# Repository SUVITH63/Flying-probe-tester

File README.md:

# FPTester

> **Automated Flying Probe PCB Evaluation & Kinematics Engine**

**FPTester** is an automated dual-arm flying probe PCB evaluation application. It parses KiCad (`.kicad_pcb`) and Gerber (`.gbr`) design files, generates hardware-ready test plan sequences, and provides a 2D dual 5-bar linkage kinematics visualizer with interactive flex handles.

---

## 💾 Direct 1-Click Downloads & Releases

Click below to download the application for your operating system:

| Operating System | Direct Download Link | Format | Launch Instructions |
| :--- | :--- | :--- | :--- |
| 🪟 **Windows** | [**Download FPTester for Windows (.zip)**](https://github.com/SUVITH63/Flying-probe-tester/releases/download/v1.1.0/FPTester-Windows-x64.zip) | 1-Click Portable `.zip` | Extract zip and double-click `start_windows.bat` or `FPTester-Launcher.bat` |
| 🪟 **Windows** | [**Download Standalone FPTester.exe**](https://github.com/SUVITH63/Flying-probe-tester/releases/download/v1.1.0/FPTester-Windows.exe) | Single Executable `.exe` | Double-click `FPTester-Windows.exe` |
| 🍎 **macOS** | [**Download FPTester for macOS (.zip)**](https://github.com/SUVITH63/Flying-probe-tester/releases/download/v1.1.0/FPTester-macOS-1Click.zip) | Standalone `.zip` | Extract zip and double-click `start_mac.command` |

> 🍎 **Mac Gatekeeper Tip**: If macOS displays *"Apple could not verify FPTester-App"*, double-click **`start_mac.command`** (which automatically unlocks it) OR right-click `FPTester-App` -> select **Open** -> click **Open Anyway**.

---

## ✨ Key Features

- **Embedded Local LLM Engine (`llm/local_llm.py`)**: Zero-dependency offline AI inference for power rails, GND, I2C pull-ups, and signal traces out of the box without requiring API keys or external Ollama setup.
- **Built-in Zero-Dependency Web Engine**: Native HTTP server running out-of-the-box on port 8000.
- **Dual 5-Bar Kinematics Visualizer**: Interactive canvas with real-time inverse kinematics, articulated elbow joints, and drag-and-drop flex handles.
- **Hardware & Simulation Support**: Interactive probe execution and ESP32 USB hardware dispatch protocol.

---

## 🚀 Running from Source

```bash
git clone https://github.com/SUVITH63/Flying-probe-tester.git
cd Flying-probe-tester

# Launch cross-platform application
python3 run_app.py
```

### OS Specific Launchers
- **Windows**: Double-click `start_windows.bat` or `FPTester-Launcher.bat`
- **macOS / Linux**: Double-click `start_mac.command` or `./start_mac_linux.sh`

Application will open automatically in your web browser at **http://localhost:8000**.

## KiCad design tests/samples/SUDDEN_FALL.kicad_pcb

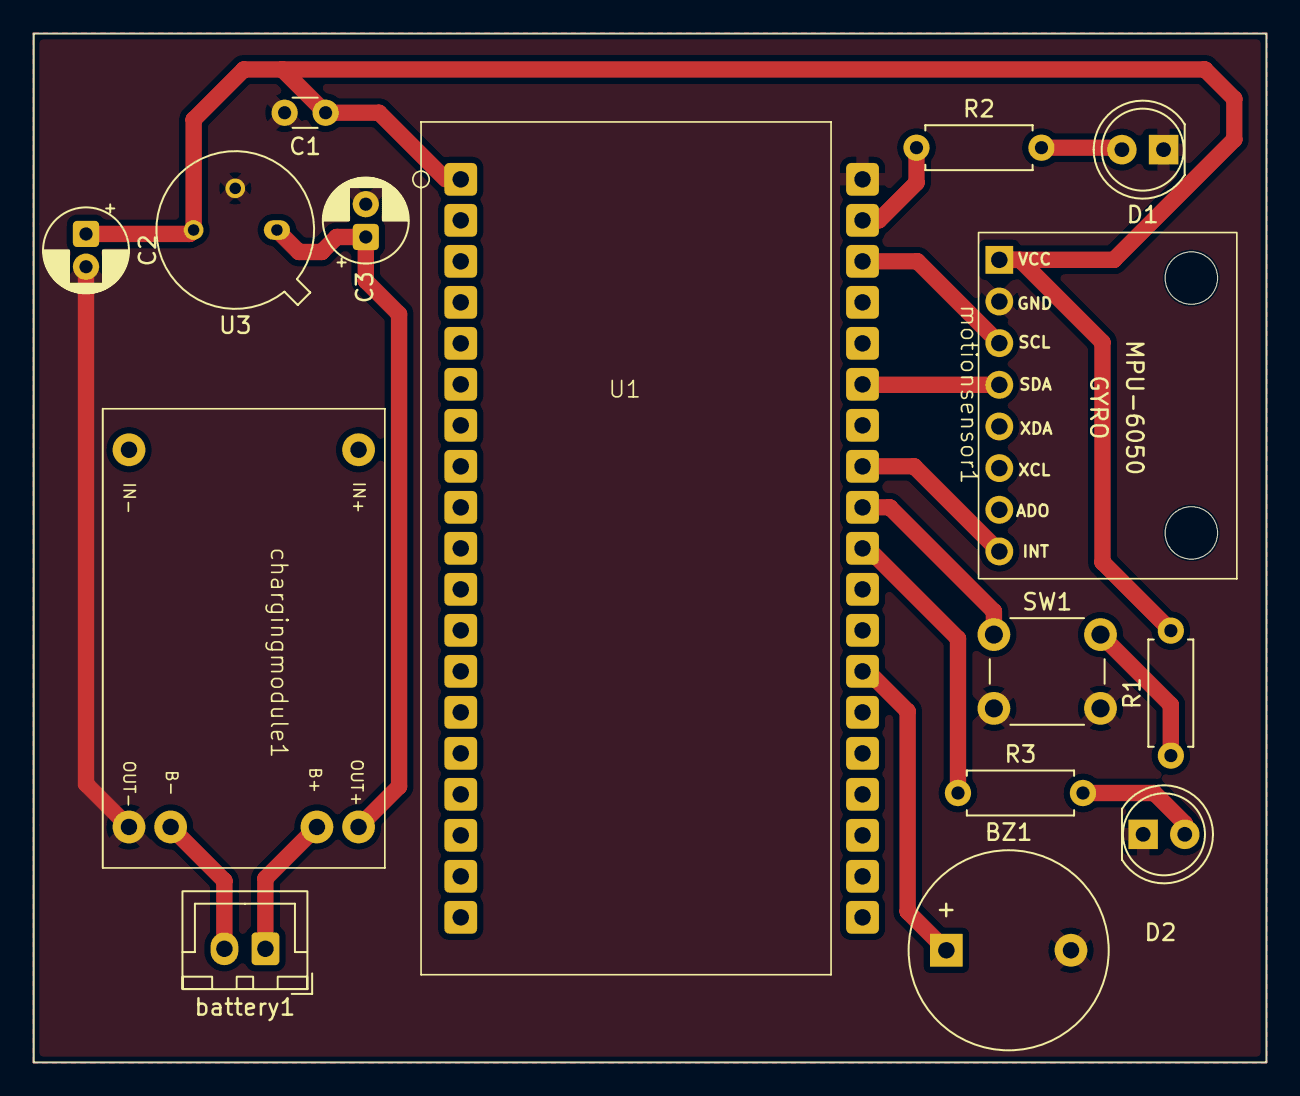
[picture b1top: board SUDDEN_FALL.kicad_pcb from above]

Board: 2 copper layers, 75.2 x 62.8 mm, 15 parts (0 on the bottom side), 15 nets.

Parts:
BZ1: Buzzer; Buzzer_12x9.5RM7.6
C1: 0.1uF; C_Disc_D3.0mm_W1.6mm_P2.50mm
C2, C3: 10uF; CP_Radial_D5.0mm_P2.00mm
D1: red LED; LED_D5.0mm
D2: green LED; LED_D5.0mm
R1: 10K; R_Axial_DIN0207_L6.3mm_D2.5mm_P7.62mm_Horizontal
R2, R3: 2.2K; R_Axial_DIN0207_L6.3mm_D2.5mm_P7.62mm_Horizontal
SW1: SW_Push_Dual; SW_PUSH_6mm
U1: ESP32 CP2102; NEW ESP 38PIN
U3: LM117_TO39; TO-39-3
battery1: Conn_01x02; JST_XH_B2B-XH-A_1x02_P2.50mm_Vertical
chargingmodule1: Conn_01x06; TP-4056
motionsensor1: Conn_01x08; GYRO MIRRORED NEW

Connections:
GND: BZ1.2 (-), C1.2, C2.2, C3.2, D1.1 (K), D2.1 (K), SW1.3, SW1.4, U1.38 (GND), U3.2 (GND), chargingmodule1.4 (OUT-), motionsensor1.2 (GND)
unnamed: BZ1.1 (+), U1.26 (GPIO4)
unnamed: D1.2 (A), R2.2
unnamed: D2.2 (A), R3.2
unnamed: R1.1, SW1.2
unnamed: C1.1, C2.1, R1.2, U1.1 (3V3), U3.3 (VO), motionsensor1.1 (VCC)
unnamed: R3.1, U1.29 (GPIO5)
unnamed: SW1.1, U1.30 (GPIO18)
unnamed: U1.31 (GPIO19), motionsensor1.8 (INT)
unnamed: U1.33 (GPIO21), motionsensor1.4 (SDA)
unnamed: U1.36 (GPIO22), motionsensor1.3 (SCL)
unnamed: R2.1, U1.37 (GPIO23)
unnamed: C3.1, U3.1 (VI), chargingmodule1.3 (OUT+)
unnamed: battery1.1 (B+), chargingmodule1.5 (B+)
unnamed: battery1.2 (B-), chargingmodule1.6 (B-)

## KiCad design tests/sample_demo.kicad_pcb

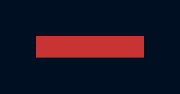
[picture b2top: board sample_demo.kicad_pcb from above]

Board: 0 copper layers, 3 parts (0 on the bottom side), 2 nets, no tracks yet.

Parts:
C1: 100nF; C_0805_2012Metric
R1, R2: 10k; R_0805_2012Metric

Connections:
+3V3: C1.2, R1.2, R2.2
SDA: R1.1, R2.1

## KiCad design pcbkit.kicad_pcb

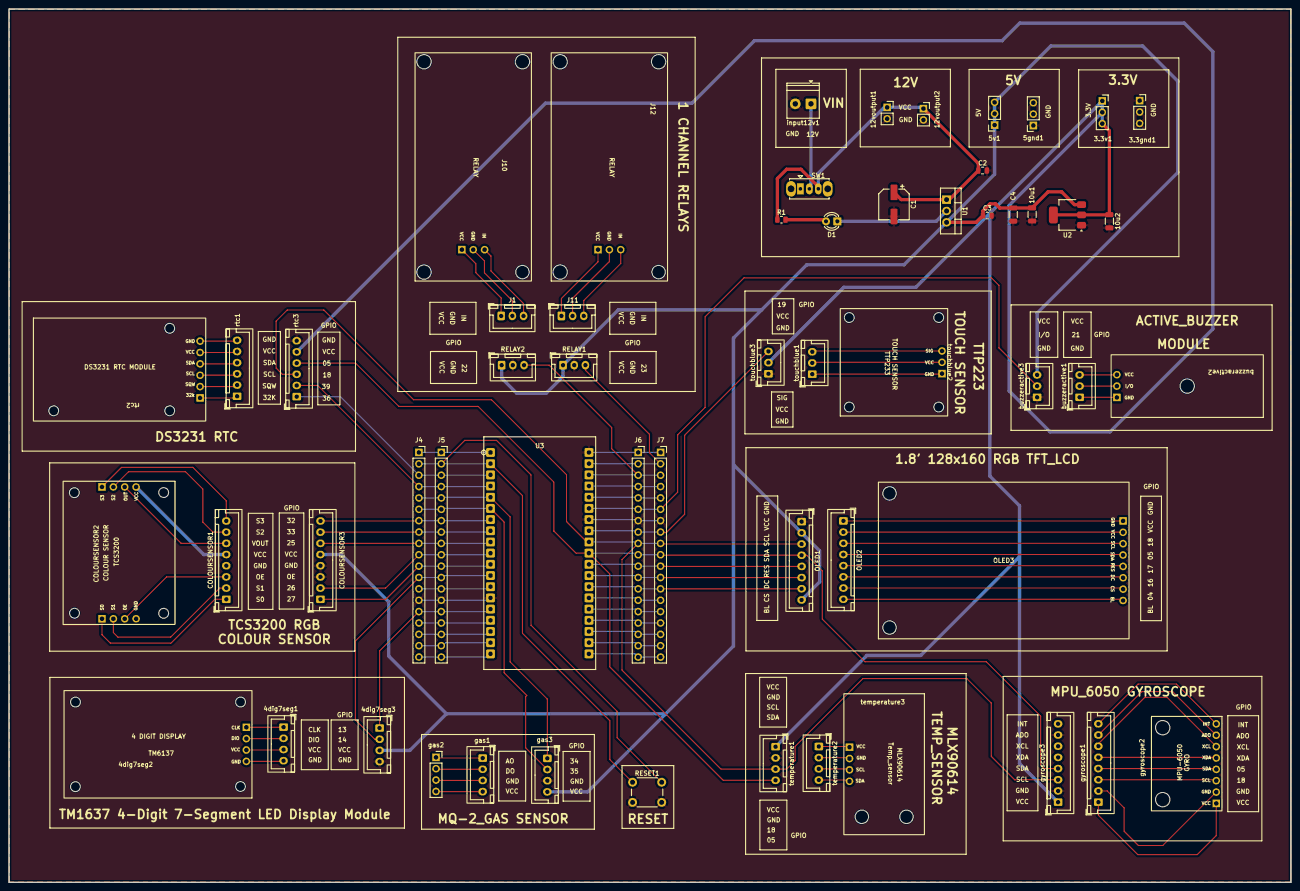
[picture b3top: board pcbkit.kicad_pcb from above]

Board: 2 copper layers, 286.4 x 195.1 mm, 57 parts (0 on the bottom side), 95 nets.

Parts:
3.3gnd1, 3.3v1, 5gnd1, 5v1: Conn_01x03; PinSocket_1x03_P2.54mm_Vertical
4dig7seg1, 4dig7seg3: Conn_01x04; JST_XH_B4B-XH-A_1x04_P2.50mm_Vertical
4dig7seg2: Conn_01x04; 4digit display
10u1, 10u2: C_Small_US; C_1206_3216Metric
12voutput1, 12voutput2: Conn_01x02; PinSocket_1x02_P2.54mm_Vertical
C1: 220u; CP_Elec_6.3x7.7
C2: 0.33uF; C_0805_2012Metric
C3: 0.1uF; C_0805_2012Metric
C4: 10uF; C_1206_3216Metric
COLOURSENSOR1, COLOURSENSOR3: Conn_02x04_Counter_Clockwise; JST_XH_B8B-XH-A_1x08_P2.50mm_Vertical
COLOURSENSOR2: Conn_02x04_Counter_Clockwise; coloursensor final
D1: LED; LED_D3.0mm
J1, J11: Conn_01x03; JST_XH_B3B-XH-A_1x03_P2.50mm_Vertical
J4, J5, J6, J7: Conn_01x19; PinSocket_1x19_P2.54mm_Vertical
J10, J12: Conn_01x03; relay1
OLED1, OLED2: Conn_01x08; JST_XH_B8B-XH-A_1x08_P2.50mm_Vertical
OLED3: Conn_01x08; OLED128x160 1.8inch tft module
R1: 560; R_0805_2012Metric
RELAY1, RELAY2: Conn_01x03; JST_XH_B3B-XH-A_1x03_P2.50mm_Vertical
RESET1: SW_Push_Dual; SW_PUSH_6mm
SW1: SW_SPDT; SW_Slide_SPDT_Straight_CK_OS102011MS2Q
U1: LM7805_TO220; TO-220-3_Vertical
U2: LM1117S-3.3; SOT-223-3_TabPin2
U3: ESP32 CP2102; ESP32_38Pin
buzzeractive1, buzzeractive3: Conn_01x03; JST_XH_B3B-XH-A_1x03_P2.50mm_Vertical
buzzeractive2: Conn_01x03; buzzer_finalmodule
gas1, gas3: Conn_01x04; JST_XH_B4B-XH-A_1x04_P2.50mm_Vertical
gas2: Conn_01x04; PinSocket_1x04_P2.54mm_Vertical
gyroscope1, gyroscope3: Conn_01x08; JST_XH_B8B-XH-A_1x08_P2.50mm_Vertical
gyroscope2: Conn_01x08; GYROSCOPE_MODULE
input12v1: Conn_01x02; TerminalBlock_Phoenix_PT-1,5-2-3.5-H_1x02_P3.50mm_Horizontal
rtc1, rtc3: Conn_01x06; JST_XH_B6B-XH-A_1x06_P2.50mm_Vertical
rtc2: Conn_01x06; RTC
temperature1, temperature2: Conn_01x04; JST_XH_B4B-XH-A_1x04_P2.50mm_Vertical
temperature3: Conn_01x04; MLX90614
touchblue1, touchblue3: Conn_01x03; JST_XH_B3B-XH-A_1x03_P2.50mm_Vertical
touchblue2: Conn_01x03; TPP233

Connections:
GND: 3.3gnd1.1 (GND), 3.3gnd1.2 (GND), 3.3gnd1.3 (GND), 4dig7seg3.4 (GND), 5gnd1.1 (GND), 5gnd1.2 (GND), 5gnd1.3 (GND), 10u1.2, 10u2.2, 12voutput1.2 (GND), 12voutput2.2 (GND), C1.2, C2.2, C3.2, C4.2, COLOURSENSOR3.3 (OE), COLOURSENSOR3.4 (GND), D1.1 (K), J4.14, J5.14, J6.1, J6.7, J7.1, J7.7 (87Pin_7), OLED1.1 (GND), RELAY1.2 (GND), RELAY2.2 (GND), RESET1.2 (GND), U1.2 (GND), U2.1 (GND), U3.14 (GND), U3.32 (GND), U3.38 (GND), buzzeractive3.1 (GND), gas3.3 (GND), gyroscope3.2 (GND), gyroscope3.7 (ADD), input12v1.2 (GND), rtc3.6 (GND), temperature1.2 (GND), touchblue3.1 (GND)
unnamed: 4dig7seg1.1 (CLK), 4dig7seg2.1 (CLK)
unnamed: 4dig7seg1.2 (DIO), 4dig7seg2.2 (DIO)
unnamed: 4dig7seg1.4 (GND), 4dig7seg2.4 (GND)
unnamed: 4dig7seg1.3 (VCC), 4dig7seg2.3 (VCC)
unnamed: 4dig7seg3.1 (CLK), J4.15, J5.15, U3.15 (GPIO13)
unnamed: 4dig7seg3.2 (DIO), J4.12, J5.12, U3.12 (GPIO14)
unnamed: 4dig7seg3.3 (VCC), 5v1.1 (5V), 5v1.2 (5V), 5v1.3 (5V), 10u1.1, C3.1, C4.1, COLOURSENSOR3.5 (VCC), OLED1.2 (VCC), OLED1.8 (BL), RELAY1.1 (VCC), RELAY2.1 (VCC), U1.3 (VO), U2.3 (VI), buzzeractive3.3 (VCC), gas3.4 (VCC)
unnamed: 12voutput1.1 (12V_OUT), 12voutput2.1 (12V_OUT), C1.1, C2.1, R1.1, SW1.3 (C), U1.1 (VI)
unnamed: COLOURSENSOR1.4 (GND), COLOURSENSOR2.4 (GND)
unnamed: COLOURSENSOR1.3 (OE), COLOURSENSOR2.3 (OE)
unnamed: COLOURSENSOR1.2 (S1), COLOURSENSOR2.2 (S1)
unnamed: COLOURSENSOR1.7 (S2), COLOURSENSOR2.7 (S2)
unnamed: COLOURSENSOR1.8 (S3), COLOURSENSOR2.8 (S3)
unnamed: COLOURSENSOR1.1 (SO), COLOURSENSOR2.1 (SO)
unnamed: COLOURSENSOR1.5 (VCC), COLOURSENSOR2.5 (VCC)
unnamed: COLOURSENSOR1.6 (VOUT), COLOURSENSOR2.6 (VOUT)
unnamed: COLOURSENSOR3.2 (S1), J4.10, J5.10, U3.10 (GPIO26)
unnamed: COLOURSENSOR3.7 (S2), J4.8, J5.8, U3.8 (GPIO33)
unnamed: COLOURSENSOR3.8 (S3), J4.7, J5.7, U3.7 (GPIO32)
unnamed: COLOURSENSOR3.1 (SO), J4.11, J5.11, U3.11 (GPIO27)
unnamed: COLOURSENSOR3.6 (VOUT), J4.9, J5.9, U3.9 (GPIO25)
unnamed: D1.2 (A), R1.2
unnamed: J1.2 (GND), J10.2 (GND)
unnamed: J1.3 (IN), J10.3 (IN)
unnamed: J1.1 (VCC), J10.1 (VCC)
unnamed: J4.1, J5.1, U3.1 (3V3)
unnamed: J4.2, J5.2, RESET1.1 (EN), U3.2 (EN)
unnamed: J4.3, J5.3, U3.3 (GPIO36), rtc3.1 (32K)
unnamed: J4.4, J5.4, U3.4 (GPIO39), rtc3.2 (SQW)
unnamed: J4.5, J5.5, U3.5 (GPIO34), gas3.1 (A0)
unnamed: J4.6, J5.6, U3.6 (GPIO35), gas3.2 (DO)
unnamed: J4.13, J5.13, U3.13 (GPIO12)
unnamed: J4.16, J5.16, U3.16 (GPIO9_/_SO2)
unnamed: J4.17, J5.17, U3.17 (GPIO10__/_S03)
unnamed: J4.18, J5.18, U3.18 (GPIO11_/_CMD)
unnamed: J4.19, J5.19, U3.19 (V5)
unnamed: J6.19 (1Pin_19), J7.19, U3.20 (GPIO6_/_CLK)
unnamed: J6.2 (2Pin_2), J7.2, RELAY1.3 (IN), U3.37 (GPIO23)
unnamed: J6.3, J7.3, RELAY2.3 (IN), U3.36 (GPIO22)
unnamed: J6.4, J7.4, U3.35 (GPIO1_/_TXD)
unnamed: J6.5, J7.5, U3.34 (GPIO3_/_RXD)
unnamed: J6.6, J7.6, U3.33 (GPIO21), buzzeractive3.2 (I/O)
unnamed: J6.8, J7.8, U3.31 (GPIO19), touchblue3.3 (SIG)
unnamed: J6.9, J7.9, OLED1.3 (CLK/SCL), U3.30 (GPIO18), gyroscope3.3 (SCL), rtc3.3 (SCL), temperature1.3 (SCL)
unnamed: J6.10, J7.10 (1Pin_10), OLED1.4 (SDA/MOSI/DIN), U3.29 (GPIO5), gyroscope3.4 (SDA), rtc3.4 (SDA), temperature1.4 (SDA)
unnamed: J6.11, J7.11, OLED1.5 (RES), U3.28 (GPIO17)
unnamed: J6.12, J7.12, OLED1.6 (DC), U3.27 (GPIO16)
unnamed: J6.13, J7.13, OLED1.7 (CS), U3.26 (GPIO4)
unnamed: J6.15, J7.15, U3.24 (GPIO2)
unnamed: J6.16, J7.16, U3.23 (GPIO15)
unnamed: J6.17, J7.17, U3.22 (GPIO8__/_SD1)
unnamed: J6.18, J7.18, U3.21 (GPIO7__/_SD0)
unnamed: J6.14, J7.14, U3.25 (GPIO0)
unnamed: J11.2 (GND), J12.2 (GND)
unnamed: J11.3 (IN), J12.3 (IN)
unnamed: J11.1 (VCC), J12.1 (VCC)
unnamed: OLED2.8 (BL), OLED3.8 (BL)
unnamed: OLED2.3 (CLK/SCL), OLED3.3 (CLK/SCL)
unnamed: OLED2.7 (CS), OLED3.7 (CS)
unnamed: OLED2.6 (DC), OLED3.6 (DC)
unnamed: OLED2.1 (GND), OLED3.1 (GND)
unnamed: OLED2.5 (RES), OLED3.5 (RES)
unnamed: OLED2.4 (SDA/MOSI/DIN), OLED3.4 (SDA/MOSI/DIN)
unnamed: OLED2.2 (VCC), OLED3.2 (VCC)
unnamed: SW1.2 (B), input12v1.1 (12V_IN)
unnamed: 3.3v1.1 (3.3V), 3.3v1.2 (3.3V), 3.3v1.3 (3.3V), 10u2.1, U2.2 (VO), gyroscope3.1 (VCC), rtc3.5 (VCC), temperature1.1 (VCC), touchblue3.2 (VCC)
unnamed: buzzeractive1.1 (GND), buzzeractive2.1 (GND)
unnamed: buzzeractive1.2 (I/O), buzzeractive2.2 (I/O)
unnamed: buzzeractive1.3 (VCC), buzzeractive2.3 (VCC)
unnamed: gas1.1 (A0), gas2.1 (A0)
unnamed: gas1.2 (DO), gas2.2 (DO)
unnamed: gas1.3 (GND), gas2.3 (GND)
unnamed: gas1.4 (VCC), gas2.4 (VCC)
unnamed: gyroscope1.7 (ADD), gyroscope2.7 (ADD)
unnamed: gyroscope1.2 (GND), gyroscope2.2 (GND)
unnamed: gyroscope1.8 (INT), gyroscope2.8 (INT)
unnamed: gyroscope1.3 (SCL), gyroscope2.3 (SCL)
unnamed: gyroscope1.4 (SDA), gyroscope2.4 (SDA)
unnamed: gyroscope1.1 (VCC), gyroscope2.1 (VCC)
unnamed: gyroscope1.6 (XCL), gyroscope2.6 (XCL)
unnamed: gyroscope1.5 (XDA), gyroscope2.5 (XDA)
unnamed: rtc1.1 (32K), rtc2.1 (32K)
unnamed: rtc1.6 (GND), rtc2.6 (GND)
unnamed: rtc1.4 (SDA), rtc2.4 (SDA)
unnamed: rtc1.5 (VCC), rtc2.5 (VCC)
unnamed: rtc1.3 (SQW), rtc2.3 (SCL)
unnamed: rtc1.2 (SQW), rtc2.2 (SQW)
unnamed: temperature2.2 (GND), temperature3.2 (GND)
unnamed: temperature2.3 (SCL), temperature3.3 (SCL)
unnamed: temperature2.4 (SDA), temperature3.4 (SDA)
unnamed: temperature2.1 (VCC), temperature3.1 (VCC)
unnamed: touchblue1.1 (GND), touchblue2.1 (GND)
unnamed: touchblue1.3 (SIG), touchblue2.3 (SIG)
unnamed: touchblue1.2 (VCC), touchblue2.2 (VCC)

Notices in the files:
README.md:
License: MIT
